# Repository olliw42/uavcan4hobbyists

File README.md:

# UAVCAN For Hobbyists (UC4H)

The project aims at bringing UAVCAN devices to hobbyists at low cost.

Project web page http://www.olliw.eu/2017/uavcan-for-hobbyists/<br>
Project blog http://www.olliw.eu/2018/uavcan-for-hobbyists-blog/

This project comprises these UAVCAN nodes and devices:

<strong>UC4H GPS-Magnetometer-Barometer Node</strong><br>

<strong>UC4H PowerBrick Node</strong><br>

<strong>UC4H ESC-Actuator Node</strong><br>

<strong>UC4H RangeFinder Node</strong><br>

<strong>UC4H Display Node</strong><br>

<strong>UC4H Notify Node</strong><br>

<strong>UC4H OreoLED Node</strong><br>

<strong>UC4H IndicatorLED Node</strong><br>

<strong>UC4H UartBridge Node</strong><br>

<strong>UC4H Air/Airspeed Node</strong><br>

<strong>UC4H FunThing Node</strong><br>

<strong>UC4H MavlinkBridge</strong><br>

<strong>UC4H SLCAN Adapter</strong><br>

<strong>UC4H Cube Carrier</strong><br>

## TERMS OF USAGE / LICENCE

The material provided in the UC4H Github repository is subject to the following conditions. 

Firmware files: All firmwares are free (but not open source). Besides unlimited private use you are also granted the permission to use them for commercial purposes under the condition that (1) you don’t modify the firmware, e.g. remove or change copyright statements, (2) provide it for free, i.e. don’t charge any explicit or implicit fees to your customers, and (3) correctly and clearly cite the origin of the firmware and the project web page in any product documentation or web page. 

Hardware files: All hardware, for which material is provided, is open source hardware, under the terms of the TAPR Open Hardware License as published by the Free Hardware Foundation, see http://www.tapr.org/ohl.html. The TAPR license explicitly permits essentially unlimited commercial use, with only few conditions such as that copyright logos are not removed.

## ACKNOWLEDGMENTS

The UC4H firmwares make use of Libcanard: https://github.com/UAVCAN/libcanard .
Many thanks to the UAVCAN team, and Pavel Kirienko especially, the main author of Libcanard.

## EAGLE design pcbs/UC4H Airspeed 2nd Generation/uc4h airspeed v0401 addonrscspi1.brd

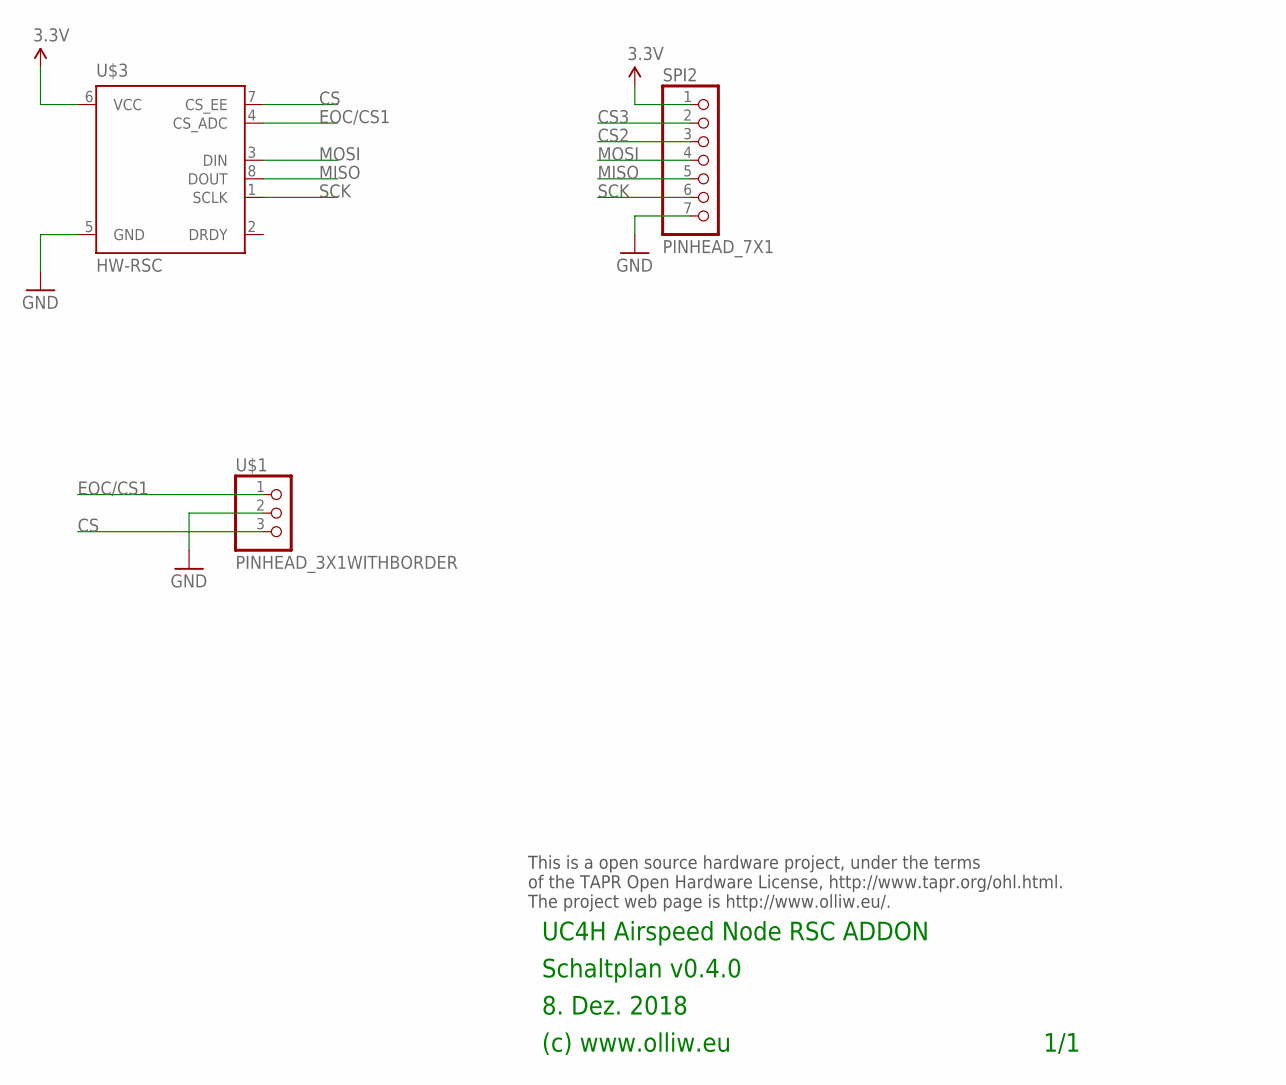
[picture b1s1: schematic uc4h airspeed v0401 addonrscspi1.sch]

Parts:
SPI2: PINHEAD_7X1
U$1: PINHEAD_3X1WITHBORDER; PINHEAD_3X1
U$3: HW-RSC; HONEYWELL-8

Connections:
3.3V: SPI2.1, U$3.6 (VCC)
CS: U$1.3 (5), U$3.7 (CS_EE)
CS2: SPI2.3
CS3: SPI2.2
EOC/CS1: U$1.1, U$3.4 (CS_ADC)
GND: SPI2.7, U$1.2 (3), U$3.5 (GND)
MISO: SPI2.5, U$3.8 (DOUT)
MOSI: SPI2.4, U$3.3 (DIN)
SCK: SPI2.6, U$3.1 (SCLK)

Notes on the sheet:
8. Dez. 2018
(c) www.olliw.eu
UC4H Airspeed Node RSC ADDON
Schaltplan v0.4.0
This is a open source hardware project, under the terms of the TAPR Open Hardware License, http://www.tapr.org/ohl.html. The project web page is http://www.olliw.eu/.
1/1

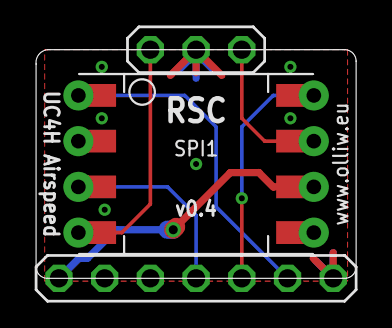
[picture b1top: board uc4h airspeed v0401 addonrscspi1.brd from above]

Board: 2 copper layers, 17.8 x 12.7 mm, 3 parts (0 on the bottom side), 7 nets.

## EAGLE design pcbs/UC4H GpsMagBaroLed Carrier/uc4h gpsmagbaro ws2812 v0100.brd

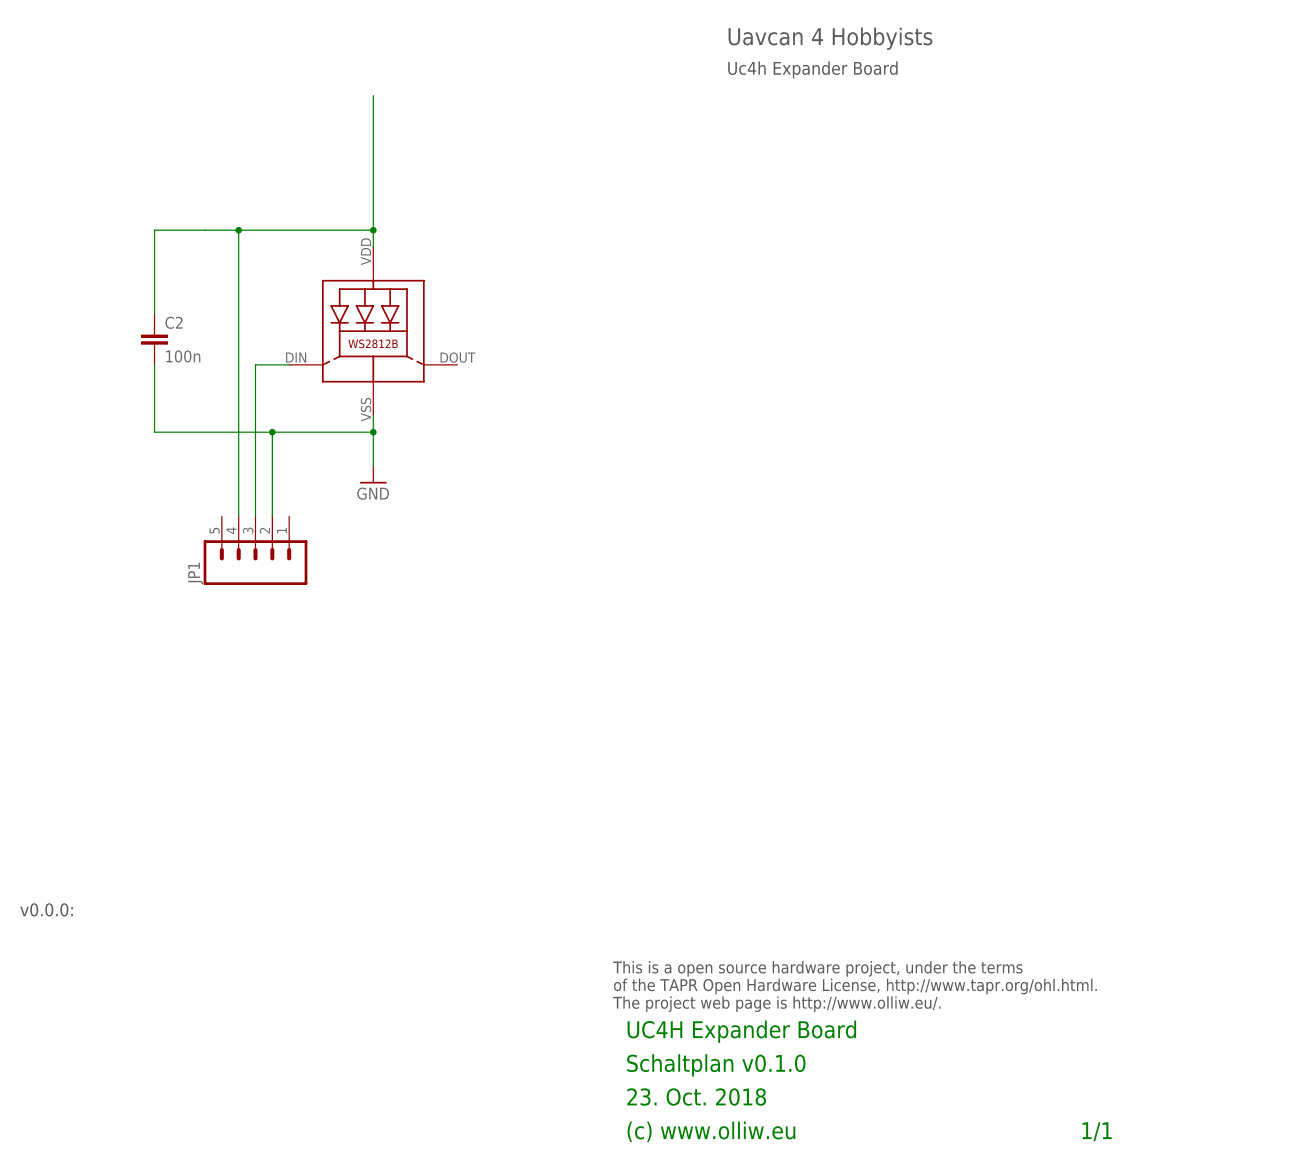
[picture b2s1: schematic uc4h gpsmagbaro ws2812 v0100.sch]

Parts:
C2: 100n; C0402
JP1: M05PTH; 1X05
LED1: WS2812B

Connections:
GND: C2.2, JP1.2, LED1.VSS (GND)
unnamed: JP1.3, LED1.DIN (DI)
unnamed: C2.1, JP1.4, LED1.VDD

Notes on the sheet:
23. Oct. 2018
(c) www.olliw.eu
UC4H Expander Board
Schaltplan v0.1.0
This is a open source hardware project, under the terms of the TAPR Open Hardware License, http://www.tapr.org/ohl.html. The project web page is http://www.olliw.eu/.
1/1
Uc4h Expander Board
Uavcan 4 Hobbyists
v0.0.0:

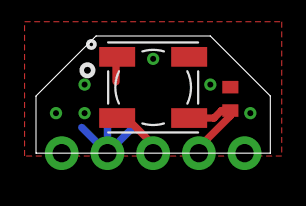
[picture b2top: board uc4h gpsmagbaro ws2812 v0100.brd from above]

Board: 2 copper layers, 13.0 x 6.5 mm, 3 parts (0 on the bottom side), 3 nets.

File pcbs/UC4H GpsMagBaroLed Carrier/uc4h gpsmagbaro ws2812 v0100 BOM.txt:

Stückliste exportiert aus C:/Users/Olli/Documents/GitHub/uavcan4hobbyists/pcbs/UC4H GpsMagBaroLed Carrier/uc4h gpsmagbaro ws2812 v0100.sch am 06.04.2019 08:57

Part Value   Device    Package Description                
C2   100n    C-EUC0402 C0402   CAPACITOR, European symbol 
JP1          M05PTH    1X05    Header 5                   
LED1 WS2812B WS2812B   WS2812B Features and Benefits

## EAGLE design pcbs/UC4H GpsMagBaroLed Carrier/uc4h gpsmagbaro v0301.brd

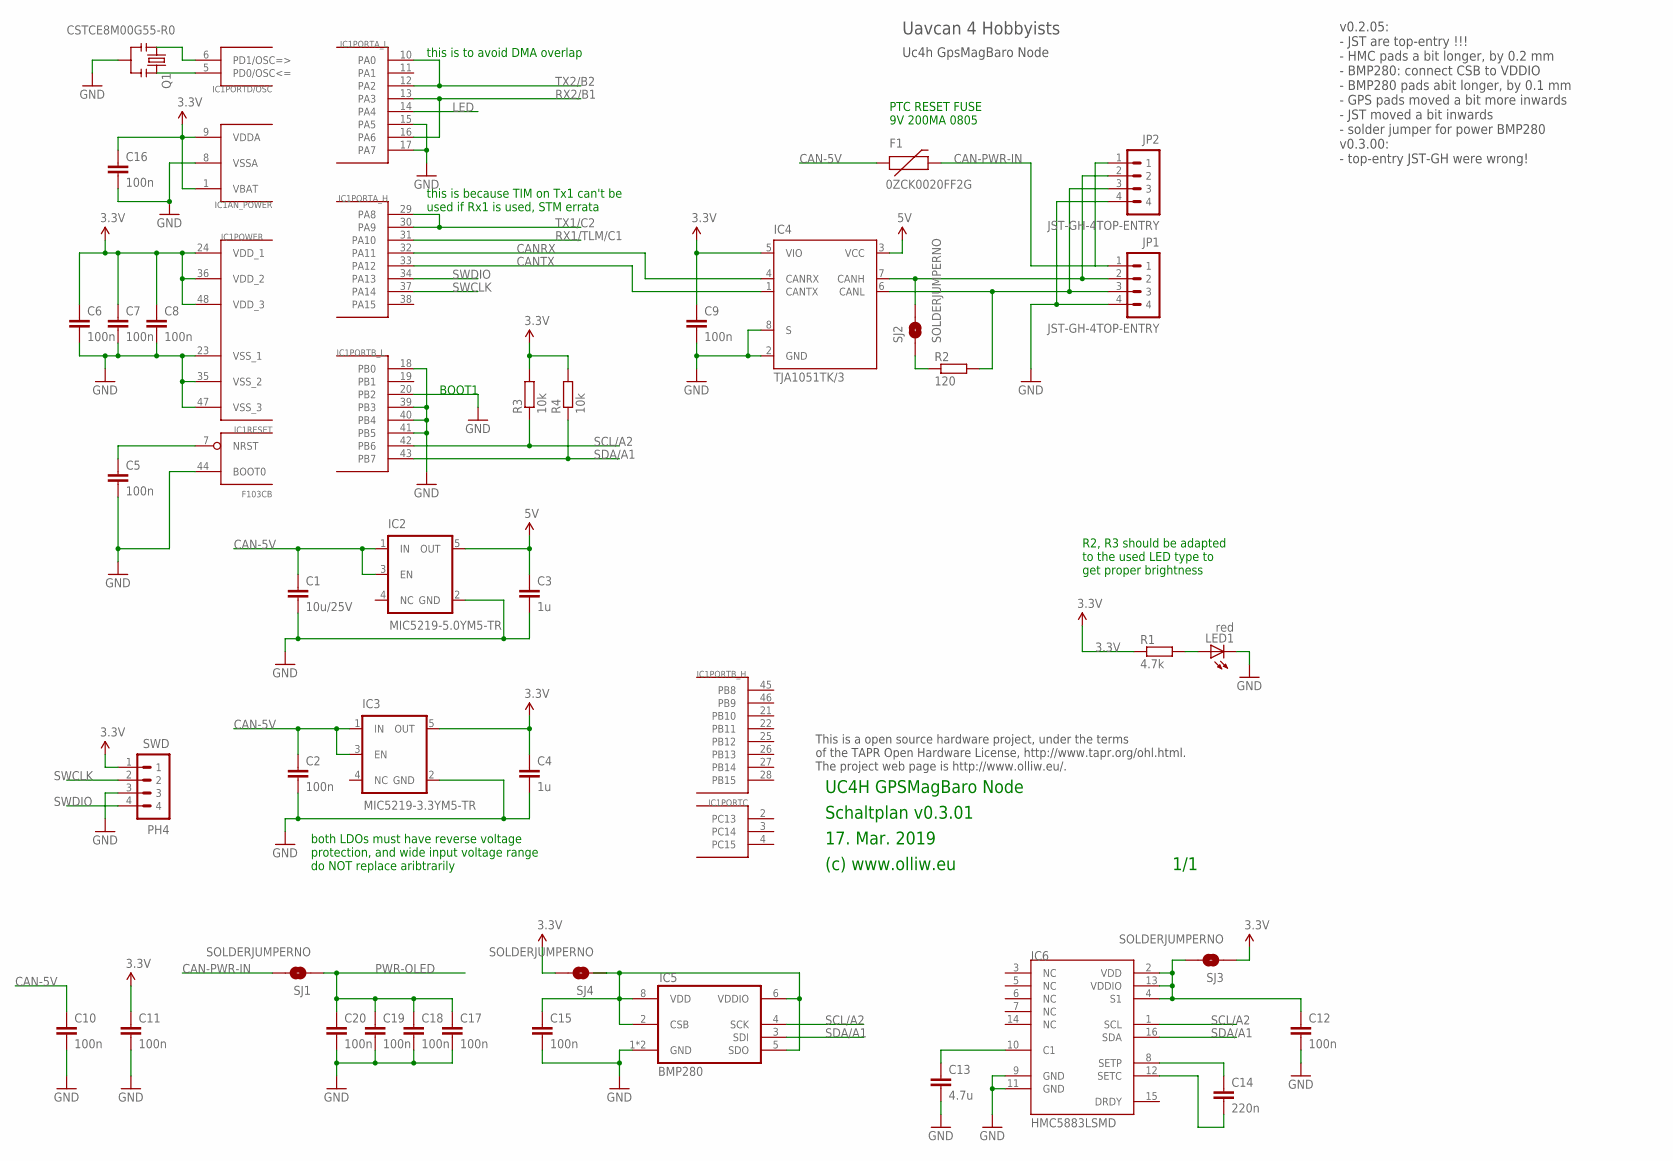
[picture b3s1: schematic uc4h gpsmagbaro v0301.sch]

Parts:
C1: 10u/25V; C1206
C2, C5, C6, C7, C8, C9: 100n; C0603K
C3, C4: 1u; C0603K
C10, C11, C12, C15, C16, C17, C18, C19, C20: 100n; C0603
C13: 4.7u; C0805
C14: 220n; C0603
F1: 0ZCK0020FF2G; FUSE-0805
IC1: F103CB; TQFP48
IC2: MIC5219-5.0YM5-TR; SOT23-5
IC3: MIC5219-3.3YM5-TR; SOT23-5
IC4: TJA1051TK/3; HVSON8
IC5: BMP280
IC6: HMC5883LSMD; 16LPCC
JP1, JP2: JST-GH-4TOP-ENTRY; BM04B-GHS-TBT
LED1: red; CHIPLED_0603
Q1: CSTCE8M00G55-R0; RESONATOR-SMD
R1: 4.7k; R0603
R2: 120; R0603
R3, R4: 10k; R0603
SJ1, SJ2, SJ3, SJ4: SOLDERJUMPERNO; SJ_2S-NO
SWD: PH4; 4X1_1P27_OCT_BILEX

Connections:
3.3V: C4.1, C6.1, C7.1, C8.1, C9.1, C11.1, C16.1, IC1.1 (VBAT), IC1.9 (VDDA), IC1.24 (VDD_1), IC1.36 (VDD_2), IC1.48 (VDD_3), IC3.5 (OUT), IC4.5 (VIO), R1.1, R3.2, R4.2, SJ3.1, SJ4.2, SWD.1
5V: C3.1, IC2.5 (OUT), IC4.3 (VCC)
CAN-5V: C1.1, C2.1, C10.1, F1.1, IC2.1 (IN), IC2.3 (EN), IC3.1 (IN), IC3.3 (EN)
CAN-PWR-IN: F1.2, JP1.1, JP2.1, SJ1.2
CANH: IC4.7 (CANH), JP1.2, JP2.2, SJ2.2
CANL: IC4.6 (CANL), JP1.3, JP2.3, R2.2
CANRX: IC1.32 (PA11), IC4.4 (CANRX)
CANTX: IC1.33 (PA12), IC4.1 (CANTX)
GND: C1.2, C2.2, C3.2, C4.2, C5.2, C6.2, C7.2, C8.2, C9.2, C10.2, C11.2, C12.2, C13.2, C15.2, C16.2, C17.2, C18.2, C19.2, C20.2, IC1.8 (VSSA), IC1.15 (PA5), IC1.17 (PA7), IC1.18 (PB0), IC1.20 (PB2), IC1.23 (VSS_1), IC1.35 (VSS_2), IC1.39 (PB3), IC1.40 (PB4), IC1.41 (PB5), IC1.44 (BOOT0), IC1.47 (VSS_3), IC2.2 (GND), IC3.2 (GND), IC4.2 (GND), IC4.8 (S), IC5.1 (GND), IC5.7 (GND), IC6.9 (GND), IC6.11 (GND), JP1.4, JP2.4, LED1.C, Q1.2, SWD.3
LED: IC1.14 (PA4)
unnamed: C5.1, IC1.7 (NRST)
unnamed: C12.1, IC6.2 (VDD), IC6.4 (S1), IC6.13 (VDDIO), SJ3.2
unnamed: R2.1, SJ2.1
unnamed: IC1.6 (PD1/OSC=>), Q1.1
unnamed: IC1.5 (PD0/OSC<=), Q1.3
unnamed: C14.1, IC6.8 (SETP)
unnamed: C15.1, IC5.2 (CSB), IC5.5 (SDO), IC5.6 (VDDIO), IC5.8 (VDD), SJ4.1
unnamed: LED1.A, R1.2
unnamed: C14.2, IC6.12 (SETC)
unnamed: C13.1, IC6.10 (C1)
PWR-OLED: C17.1, C18.1, C19.1, C20.1, SJ1.1
RX1/TLM/C1: IC1.31 (PA10)
RX2/B1: IC1.13 (PA3), IC1.16 (PA6)
SCL/A2: IC1.42 (PB6), IC5.4 (SCK), IC6.1 (SCL), R3.1
SDA/A1: IC1.43 (PB7), IC5.3 (SDI), IC6.16 (SDA), R4.1
SWCLK: IC1.37 (PA14), SWD.2
SWDIO: IC1.34 (PA13), SWD.4
TX1/C2: IC1.29 (PA8), IC1.30 (PA9)
TX2/B2: IC1.10 (PA0), IC1.12 (PA2)

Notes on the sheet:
17. Mar. 2019
(c) www.olliw.eu
UC4H GPSMagBaro Node
Schaltplan v0.3.01
This is a open source hardware project, under the terms of the TAPR Open Hardware License, http://www.tapr.org/ohl.html. The project web page is http://www.olliw.eu/.
1/1
Uc4h GpsMagBaro Node
Uavcan 4 Hobbyists
BOOT1
PTC RESET FUSE 9V 200MA 0805
both LDOs must have reverse voltage protection, and wide input voltage range do NOT replace aribtrarily
this is to avoid DMA overlap
this is because TIM on Tx1 can't be used if Rx1 is used, STM errata
v0.2.05: - JST are top-entry !!! - HMC pads a bit longer, by 0.2 mm - BMP280: connect CSB to VDDIO - BMP280 pads abit longer, by 0.1 mm - GPS pads moved a bit more inwards - JST moved a bit inwards - solder jumper for power BMP280 v0.3.00: - top-entry JST-GH were wrong!
R2, R3 should be adapted to the used LED type to get proper brightness

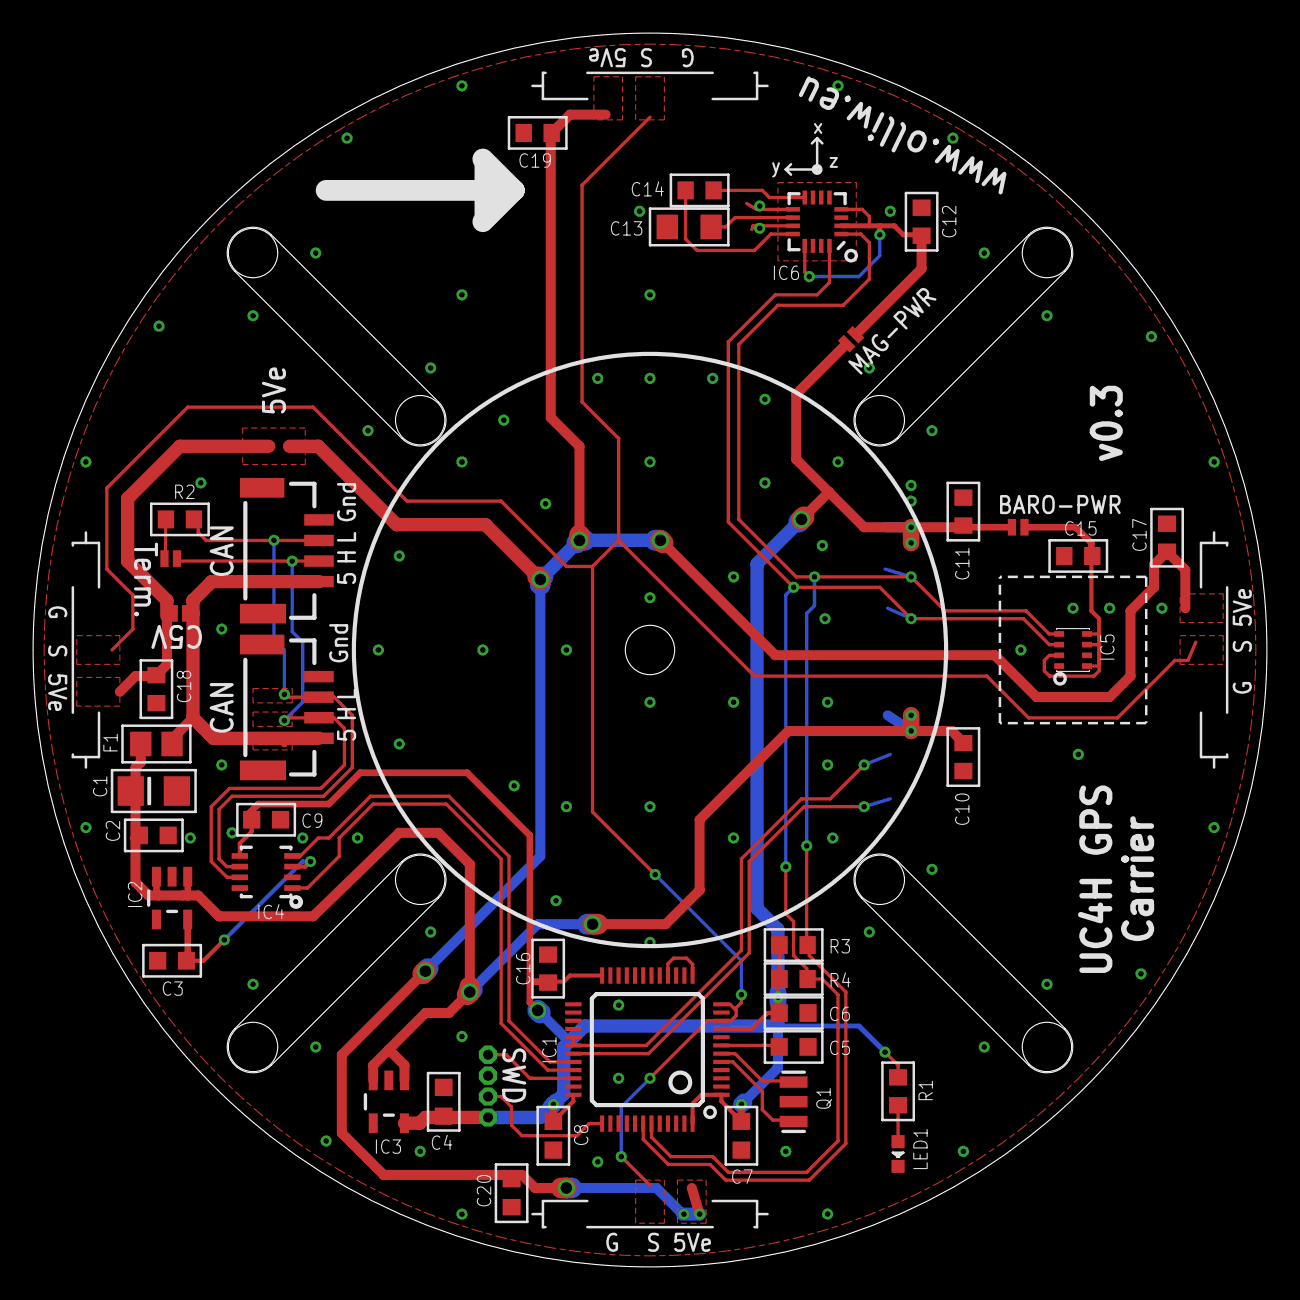
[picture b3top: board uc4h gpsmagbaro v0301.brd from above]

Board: 2 copper layers, 75.0 x 75.0 mm, 40 parts (0 on the bottom side), 27 nets.

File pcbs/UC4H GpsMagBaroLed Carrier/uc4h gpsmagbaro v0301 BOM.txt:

Stückliste exportiert aus C:/Users/Olli/Documents/GitHub/uavcan4hobbyists/pcbs/UC4H GpsMagBaroLed Carrier/uc4h gpsmagbaro v0301.sch am 06.04.2019 08:56

Part Value             Device                Package            Description                                           
C1   10u/25V           C-EUC1206             C1206              CAPACITOR, European symbol                            
C2   100n              C-EUC0603K            C0603K             CAPACITOR, European symbol                            
C3   1u                C-EUC0603K            C0603K             CAPACITOR, European symbol                            
C4   1u                C-EUC0603K            C0603K             CAPACITOR, European symbol                            
C5   100n              C-EUC0603K            C0603K             CAPACITOR, European symbol                            
C6   100n              C-EUC0603K            C0603K             CAPACITOR, European symbol                            
C7   100n              C-EUC0603K            C0603K             CAPACITOR, European symbol                            
C8   100n              C-EUC0603K            C0603K             CAPACITOR, European symbol                            
C9   100n              C-EUC0603K            C0603K             CAPACITOR, European symbol                            
C10  100n              C-EUC0603             C0603              CAPACITOR, European symbol                            
C11  100n              C-EUC0603             C0603              CAPACITOR, European symbol                            
C12  100n              C-EUC0603             C0603              CAPACITOR, European symbol                            
C13  4.7u              C-EUC0805             C0805              CAPACITOR, European symbol                            
C14  220n              C-EUC0603             C0603              CAPACITOR, European symbol                            
C15  100n              C-EUC0603             C0603              CAPACITOR, European symbol                            
C16  100n              C-EUC0603             C0603              CAPACITOR, European symbol                            
C17  100n              C-EUC0603             C0603              CAPACITOR, European symbol                            
C18  100n              C-EUC0603             C0603              CAPACITOR, European symbol                            
C19  100n              C-EUC0603             C0603              CAPACITOR, European symbol                            
C20  100n              C-EUC0603             C0603              CAPACITOR, European symbol                            
F1   0ZCK0020FF2G      FUSE-PTCFUSE-0805     FUSE-0805                                                                
IC1  F103CB            STM32F10XCXT6         TQFP48             ST STM32F101/103 48pin LQFP                           
IC2  MIC5219-5.0YM5-TR V_REG_TPS76433SOT23-5 SOT23-5            Voltage Regulator                                     
IC3  MIC5219-3.3YM5-TR V_REG_TPS76433SOT23-5 SOT23-5            Voltage Regulator                                     
IC4  TJA1051TK/3       TJA1051TK/3           HVSON8                                                                   
IC5  BMP280            BMP280                BMP280             The BMP280 is an absolute barometric pressure sensor. 
IC6  HMC5883LSMD       HMC5883LSMD           16LPCC             3 Axis Digital Compass IC                             
JP1  JST-GH-4TOP-ENTRY JST-GH-4TOP-ENTRY     BM04B-GHS-TBT                                                            
JP2  JST-GH-4TOP-ENTRY JST-GH-4TOP-ENTRY     BM04B-GHS-TBT                                                            
LED1 red               LEDCHIPLED_0603       CHIPLED_0603       LED                                                   
Q1   CSTCE8M00G55-R0   RESONATORSMD          RESONATOR-SMD      Resonator                                             
R1   4.7k              R-EU_R0603            R0603              RESISTOR, European symbol                             
R2   120               R-EU_R0603            R0603              RESISTOR, European symbol                             
R3   10k               R-EU_R0603            R0603              RESISTOR, European symbol                             
R4   10k               R-EU_R0603            R0603              RESISTOR, European symbol                             
SJ1  SOLDERJUMPERNO    SOLDERJUMPERNO        SJ_2S-NO           Solder Jumper                                         
SJ2  SOLDERJUMPERNO    SOLDERJUMPERNO        SJ_2S-NO           Solder Jumper                                         
SJ3  SOLDERJUMPERNO    SOLDERJUMPERNO        SJ_2S-NO           Solder Jumper                                         
SJ4  SOLDERJUMPERNO    SOLDERJUMPERNO        SJ_2S-NO           Solder Jumper                                         
SWD  PH4               P4X1_1P27-OCT_BILEX   4X1_1P27_OCT_BILEX

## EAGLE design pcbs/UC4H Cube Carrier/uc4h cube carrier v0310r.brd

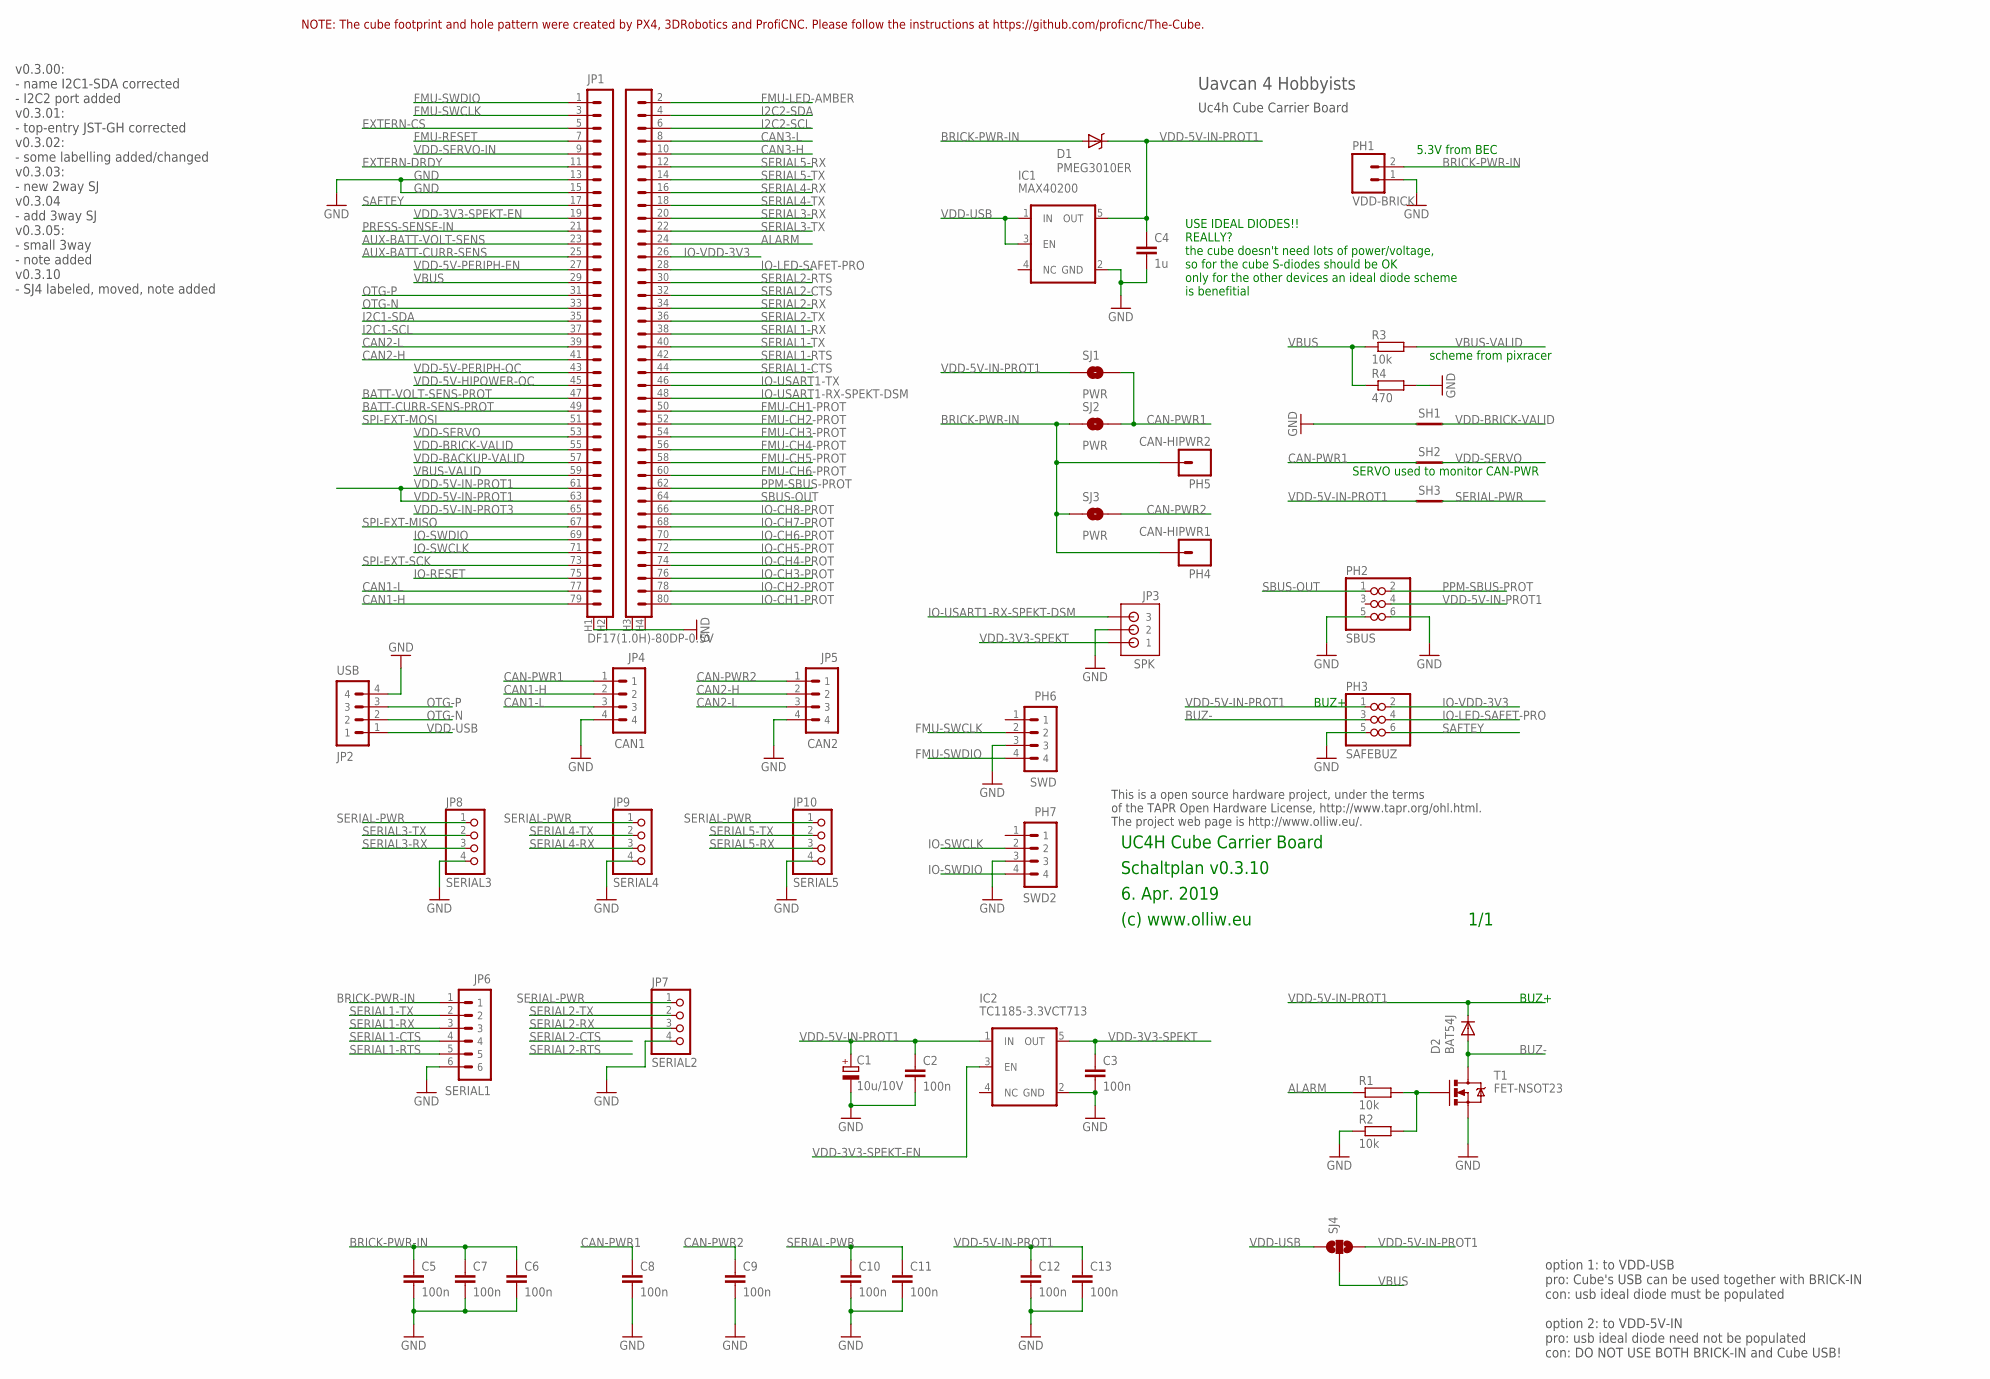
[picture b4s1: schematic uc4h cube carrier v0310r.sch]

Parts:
C1: 10u/10V; SMC_A
C2, C3, C5, C6, C8, C9, C10, C11, C12, C13: 100n; C0603
C4: 1u; C0603
C7: 100n; C0402
D1: PMEG3010ER; SOD123W-DIODE
D2: BAT54J; SOD110-R
IC1: MAX40200; SOT23-5
IC2: TC1185-3.3VCT713; SOT23-5
JP1: DF17(1.0H)-80DP-0.5V; PIX-CUBE-DF17(1.0H)-80DP-0.5V-VIA
JP2: USB; BM04B-GHS-TBT
JP3: SPK; B3B-ZR
JP4: CAN1; BM04B-GHS-TBT
JP5: CAN2; BM04B-GHS-TBT
JP6: SERIAL1; BM06B-GHS-TBT
JP7: SERIAL2; PINHEAD_4X1
JP8: SERIAL3; PINHEAD_4X1
JP9: SERIAL4; PINHEAD_4X1
JP10: SERIAL5; PINHEAD_4X1
PH1: VDD-BRICK; 1X02
PH2: SBUS; PINHEAD_3X2
PH3: SAFEBUZ; PINHEAD_3X2
PH4: CAN-HIPWR1; 1X01
PH5: CAN-HIPWR2; 1X01
PH6: SWD; 4X1_1P27_OCT_BILEX
PH7: SWD2; 4X1_1P27_OCT_BILEX
R1, R2, R3: 10k; R0402
R4: 470; R0402
SH1, SH2, SH3: SHORT-HT5; SHORT_TOP-50
SJ1, SJ3: PWR; SJ-2WAY-BIG-WPASTEC
SJ2: PWR; SJ-2WAY-BIG
SJ4: SJ-3WAY-03; SJ-3WAY-WPASTEC
T1: FET-NSOT23; SOT23

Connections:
ALARM: JP1.24, R1.1
AUX-BATT-CURR-SENS: JP1.25
AUX-BATT-VOLT-SENS: JP1.23
BATT-CURR-SENS-PROT: JP1.49
BATT-VOLT-SENS-PROT: JP1.47
BRICK-PWR-IN: C5.1, C6.1, C7.1, D1.A, JP6.1, PH1.2, PH4.1, PH5.1, SJ2.1, SJ3.1
BUZ-: D2.A, PH3.3, T1.3 (D)
CAN1-H: JP1.79, JP4.2
CAN1-L: JP1.77, JP4.3
CAN2-H: JP1.41, JP5.2
CAN2-L: JP1.39, JP5.3
CAN3-H: JP1.10
CAN3-L: JP1.8
CAN-PWR1: C8.1, JP4.1, SH2.1, SJ1.2, SJ2.2
CAN-PWR2: C9.1, JP5.1, SJ3.2
EXTERN-CS: JP1.5
EXTERN-DRDY: JP1.11
FMU-CH1-PROT: JP1.50
FMU-CH2-PROT: JP1.52
FMU-CH3-PROT: JP1.54
FMU-CH4-PROT: JP1.56
FMU-CH5-PROT: JP1.58
FMU-CH6-PROT: JP1.60
FMU-LED-AMBER: JP1.2
FMU-RESET: JP1.7
FMU-SWCLK: JP1.3, PH6.2
FMU-SWDIO: JP1.1, PH6.4
GND: C1.-, C2.2, C3.2, C4.2, C5.2, C6.2, C7.2, C8.2, C9.2, C10.2, C11.2, C12.2, C13.2, IC1.2 (GND), IC2.2 (GND), JP1.13, JP1.15, JP1.H1 (81), JP1.H2 (82), JP1.H3 (83), JP1.H4 (84), JP2.4, JP3.2, JP4.4, JP5.4, JP6.6, JP7.4, JP8.4, JP9.4, JP10.4, PH1.1, PH2.5, PH2.6, PH3.5, PH6.3, PH7.3, R2.1, R4.2, SH1.1, T1.2 (S)
I2C1-SCL: JP1.37
I2C1-SDA: JP1.35
I2C2-SCL: JP1.6
I2C2-SDA: JP1.4
IO-CH1-PROT: JP1.80
IO-CH2-PROT: JP1.78
IO-CH3-PROT: JP1.76
IO-CH4-PROT: JP1.74
IO-CH5-PROT: JP1.72
IO-CH6-PROT: JP1.70
IO-CH7-PROT: JP1.68
IO-CH8-PROT: JP1.66
IO-LED-SAFET-PRO: JP1.28, PH3.4
IO-RESET: JP1.75
IO-SWCLK: JP1.71, PH7.2
IO-SWDIO: JP1.69, PH7.4
IO-USART1-RX-SPEKT-DSM: JP1.48, JP3.3
IO-USART1-TX: JP1.46
IO-VDD-3V3: JP1.26, PH3.2
unnamed: R1.2, R2.2, T1.1 (G)
OTG-N: JP1.33, JP2.2
OTG-P: JP1.31, JP2.3
PPM-SBUS-PROT: JP1.62, PH2.2
PRESS-SENSE-IN: JP1.21
SAFTEY: JP1.17, PH3.6
SBUS-OUT: JP1.64, PH2.1
SERIAL1-CTS: JP1.44, JP6.4
SERIAL1-RTS: JP1.42, JP6.5
SERIAL1-RX: JP1.38, JP6.3
SERIAL1-TX: JP1.40, JP6.2
SERIAL2-CTS: JP1.32
SERIAL2-RTS: JP1.30
SERIAL2-RX: JP1.34, JP7.3
SERIAL2-TX: JP1.36, JP7.2
SERIAL3-RX: JP1.20, JP8.3
SERIAL3-TX: JP1.22, JP8.2
SERIAL4-RX: JP1.16, JP9.3
SERIAL4-TX: JP1.18, JP9.2
SERIAL5-RX: JP1.12, JP10.3
SERIAL5-TX: JP1.14, JP10.2
SERIAL-PWR: C10.1, C11.1, JP7.1, JP8.1, JP9.1, JP10.1, SH3.2
SPI-EXT-MISO: JP1.67
SPI-EXT-MOSI: JP1.51
SPI-EXT-SCK: JP1.73
VBUS: JP1.29, R3.1, R4.1, SJ4.2
VBUS-VALID: JP1.59, R3.2
VDD-3V3-SPEKT: C3.1, IC2.5 (OUT), JP3.1
VDD-3V3-SPEKT-EN: IC2.3 (EN), JP1.19
VDD-5V-HIPOWER-OC: JP1.45
VDD-5V-IN-PROT1: C1.+, C2.1, C4.1, C12.1, C13.1, D1.C, D2.C, IC1.5 (OUT), IC2.1 (IN), JP1.61, JP1.63, PH2.4, PH3.1, SH3.1, SJ1.1, SJ4.3
VDD-5V-IN-PROT3: JP1.65
VDD-5V-PERIPH-EN: JP1.27
VDD-5V-PERIPH-OC: JP1.43
VDD-BACKUP-VALID: JP1.57
VDD-BRICK-VALID: JP1.55, SH1.2
VDD-SERVO: JP1.53, SH2.2
VDD-SERVO-IN: JP1.9
VDD-USB: IC1.1 (IN), IC1.3 (EN), JP2.1, SJ4.1

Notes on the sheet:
6. Apr. 2019
(c) www.olliw.eu
UC4H Cube Carrier Board
Schaltplan v0.3.10
This is a open source hardware project, under the terms of the TAPR Open Hardware License, http://www.tapr.org/ohl.html. The project web page is http://www.olliw.eu/.
1/1
Uc4h Cube Carrier Board
Uavcan 4 Hobbyists
v0.3.00: - name I2C1-SDA corrected - I2C2 port added v0.3.01: - top-entry JST-GH corrected v0.3.02: - some labelling added/changed v0.3.03: - new 2way SJ v0.3.04 - add 3way SJ v0.3.05: - small 3way - note added v0.3.10 - SJ4 labeled, moved, note added
5.3V from BEC
USE IDEAL DIODES!! REALLY? the cube doesn't need lots of power/voltage, so for the cube S-diodes should be OK only for the other devices an ideal diode scheme is benefitial
SERVO used to monitor CAN-PWR
scheme from pixracer
BUZ+
NOTE: The cube footprint and hole pattern were created by PX4, 3DRobotics and ProfiCNC. Please follow the instructions at https://github.com/proficnc/The-Cube.
option 1: to VDD-USB pro: Cube's USB can be used together with BRICK-IN con: usb ideal diode must be populated option 2: to VDD-5V-IN pro: usb ideal diode need not be populated con: DO NOT USE BOTH BRICK-IN and Cube USB!

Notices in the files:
parts and their libraries:
Licensing: CC v3.0 Share-Alike You are welcome to use this library for commercial purposes.
